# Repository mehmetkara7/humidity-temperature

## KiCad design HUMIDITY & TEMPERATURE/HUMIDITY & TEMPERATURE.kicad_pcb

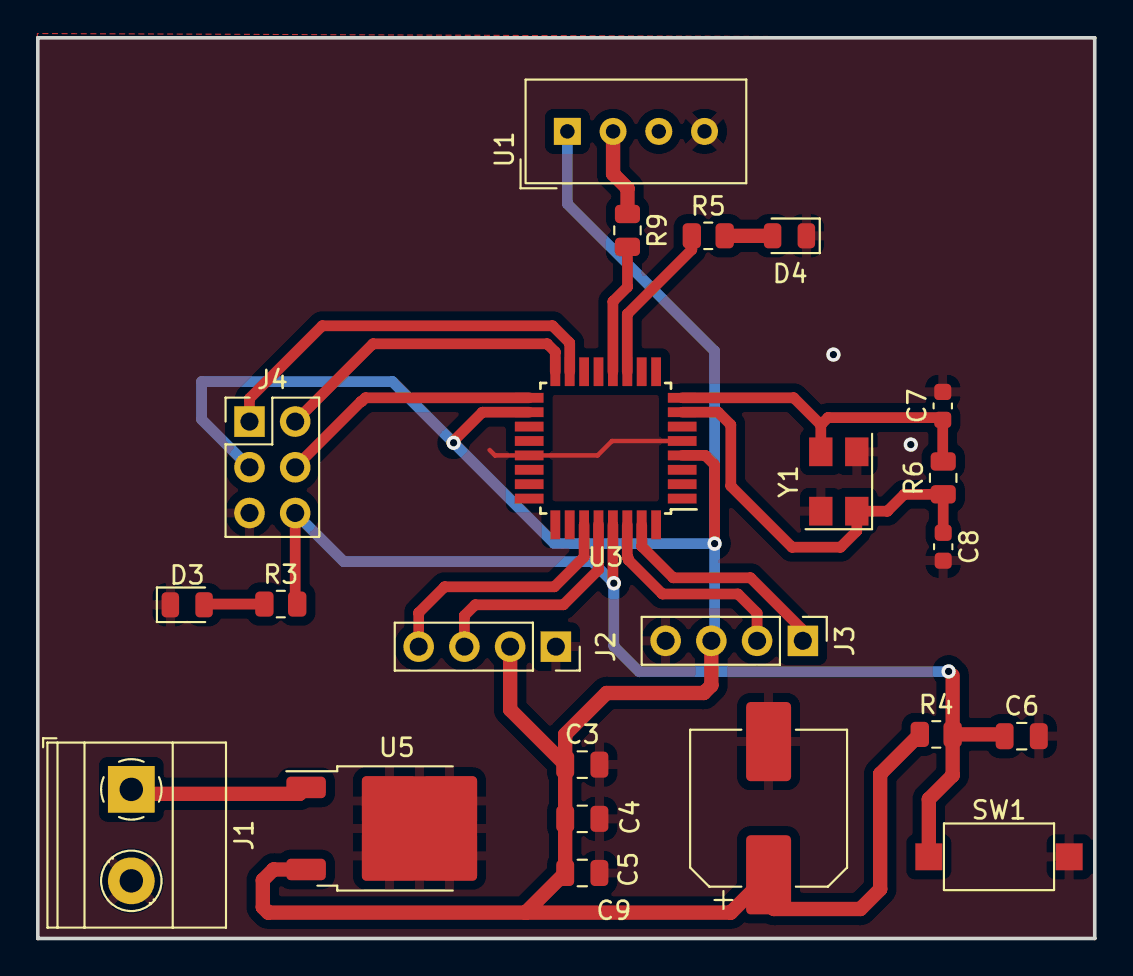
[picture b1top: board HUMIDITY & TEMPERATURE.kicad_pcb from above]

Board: 2 copper layers, 58.7 x 50.0 mm, 23 parts (0 on the bottom side), 18 nets.

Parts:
C3, C4, C5, C6: 100nF; C_0805_2012Metric
C7, C8: 18pF; C_0603_1608Metric
C9: 220UF 25V; CP_Elec_8x10.5
D3, D4: LED_Small; LED_0805_2012Metric
J1: Conn_01x02; TerminalBlock_Phoenix_MKDS-1,5-2-5.08_1x02_P5.08mm_Horizont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
J2: Conn_01x04; PinSocket_1x04_P2.54mm_Vertical
J3: UART; PinHeader_1x04_P2.54mm_Vertical
J4: ISP; PinHeader_2x03_P2.54mm_Vertical
R3: 330R; R_0805_2012Metric
R4: 4K7; R_0805_2012Metric
R5: 1K; R_0805_2012Metric
R6: 1M; R_0805_2012Metric
R9: 5k; R_0805_2012Metric
SW1: 6x6 SMD; SW_SPST_CK_RS282G05A3
U1: DHT11; Aosong_DHT11_5.5x12.0_P2.54mm
U3: ATmega328PB-A; TQFP-32_7x7mm_P0.8mm
U5: L7805; TO-252-2
Y1: 16MHz; Crystal_SMD_5032-4Pin_5.0x3.2mm

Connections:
+5V: C3.1, C4.1, C5.1, C9.1, J2.2, J3.3, J4.3, R4.1, U1.1 (VCC), U3.4 (VCC), U3.18 (AVCC), U5.3 (OUT)
GND: C3.2, C4.2, C5.2, C6.2, C7.2, C8.2, C9.2, D3.1 (K), D4.1 (K), J1.2, J2.1, J3.4, J4.5, SW1.2, U1.4 (GND), U3.5 (GND), U3.21 (GND), U5.2 (GND), Y1.2, Y1.4
LED: R5.1, U3.11 (PD7)
MISO: J4.2, U3.16 (PB4)
MOSI: J4.1, U3.15 (PB3)
unnamed: D3.2 (A), R3.1
unnamed: D4.2 (A), R5.2
unnamed: R9.1, U1.2 (IO)
PD1: R9.2, U3.12 (PB0)
RESET: C6.1, J4.6, R3.2, R4.2, SW1.1, U3.29 (~RESET/PC6)
RXD: J3.2, U3.30 (PD0)
SCK: J4.4, U3.17 (PB5)
SCL: J2.3, U3.28 (PC5)
SDA: J2.4, U3.27 (PC4)
TXD: J3.1, U3.31 (PD1)
VIN: J1.1, U5.1 (IN)
XTAL1: C8.1, R6.1, U3.7 (XTAL1/PB6), Y1.1
XTAL2: C7.1, R6.2, U3.8 (XTAL2/PB7), Y1.3
